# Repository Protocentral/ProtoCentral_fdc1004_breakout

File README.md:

Protocentral FDC1004 capacitance sensor breakout board
================================

### Don't have one? [Buy it here](https://protocentral.com/product/protocentral-fdc1004-capacitance-sensor-breakout-board/)
### Looking for a more integrated solution? [Check out our FDC1004 & ESP32-S3 based Sensything CAP](https://protocentral.com/product/protocentral-sensything-cap-wireless-pulse-sensor-kit-based-on-afe4400-esp32/)

The FDC1004 is a single-chip IC for capacitance measurement for application including proximity sensing and liquid level sensing. This is based on the concept of measuring capacitance of an electrode with respect to ground.

This breakout board contains everything to connect it to an Arduino's I2C pins and it can be connected to any other platform with support for I2C two-wire interfaces.

We have made several cool projects with it including proximity sensing and liquid-level sensing from the outside of a tank. Check out our [Hackster page](https://www.hackster.io/team-protocentral/non-contact-capacitive-liquid-level-sensing-using-fdc1004-9333c7) for the detailed project description.

## Hardware Setup
Connection with the Arduino board is as follows:

|FDC1004 pin label| Arduino Connection  |Pin Function      |
 |:-----------------: |:---------------------:|:------------------:|
 | GND                | GND                   |  GND               |
 | SCL                | A5                    |  Serial Clock      |
 | Vcc                | 5V                    |  Power             |
 | SDA                | A4                    |  Serial Data       |

## Software Features

### Multiple I2C Interface Support
The library now supports using different I2C interfaces (Wire, Wire1, etc.) on boards that have multiple I2C ports like ESP32, Arduino Mega, etc.

#### Basic Usage (Default Wire Interface)
```cpp
#include <Wire.h>
#include <Protocentral_FDC1004.h>

FDC1004 sensor(FDC1004_RATE_100HZ);

void setup() {
    Wire.begin();
    sensor.begin();
}
```

#### Custom I2C Interface Usage
```cpp
#include <Wire.h>
#include <Protocentral_FDC1004.h>

// Method 1: TwoWire pointer as first parameter
FDC1004 sensor(&Wire1, FDC1004_RATE_100HZ);

// Method 2: TwoWire pointer as third parameter
// FDC1004 sensor(FDC1004_RATE_100HZ, FDC1004_I2C_ADDRESS, &Wire1);

void setup() {
    Wire1.begin(); // or Wire1.begin(SDA_PIN, SCL_PIN) for ESP32
    sensor.begin();
}
```

## For further details, refer [the documentation on FDC1004 breakout board](https://docs.protocentral.com/getting-started-with-FDC1004/)

## Contributors & Acknowledgments

We appreciate contributions from our community that help improve this library. Special thanks to:

- **@Benicz** - For identifying and reporting the critical CAPDAC hardware configuration bug (v2.0.1).

If you've contributed to this project, please let us know!

License Information
===================

This product is open source! Both, our hardware and software are open source and licensed under the following licenses:

Hardware
---------

**All hardware is released under [Creative Commons Share-alike 4.0 International](http://creativecommons.org/licenses/by-sa/4.0/).**

You are free to:

* Share — copy and redistribute the material in any medium or format
* Adapt — remix, transform, and build upon the material for any purpose, even commercially.
The licensor cannot revoke these freedoms as long as you follow the license terms.

Under the following terms:

* Attribution — You must give appropriate credit, provide a link to the license, and indicate if changes were made. You may do so in any reasonable manner, but not in any way that suggests the licensor endorses you or your use.
* ShareAlike — If you remix, transform, or build upon the material, you must distribute your contributions under the same license as the original.

Software
--------

**All software is released under the MIT License(http://opensource.org/licenses/MIT).**

THE SOFTWARE IS PROVIDED "AS IS", WITHOUT WARRANTY OF ANY KIND, EXPRESS OR IMPLIED, INCLUDING BUT NOT LIMITED TO THE WARRANTIES OF MERCHANTABILITY, FITNESS FOR A PARTICULAR PURPOSE AND NONINFRINGEMENT. IN NO EVENT SHALL THE AUTHORS OR COPYRIGHT HOLDERS BE LIABLE FOR ANY CLAIM, DAMAGES OR OTHER LIABILITY, WHETHER IN AN ACTION OF CONTRACT, TORT OR OTHERWISE, ARISING FROM, OUT OF OR IN CONNECTION WITH THE SOFTWARE OR THE USE OR OTHER DEALINGS IN THE SOFTWARE.

Please check [*LICENSE.md*](LICENSE.md) for detailed license descriptions.

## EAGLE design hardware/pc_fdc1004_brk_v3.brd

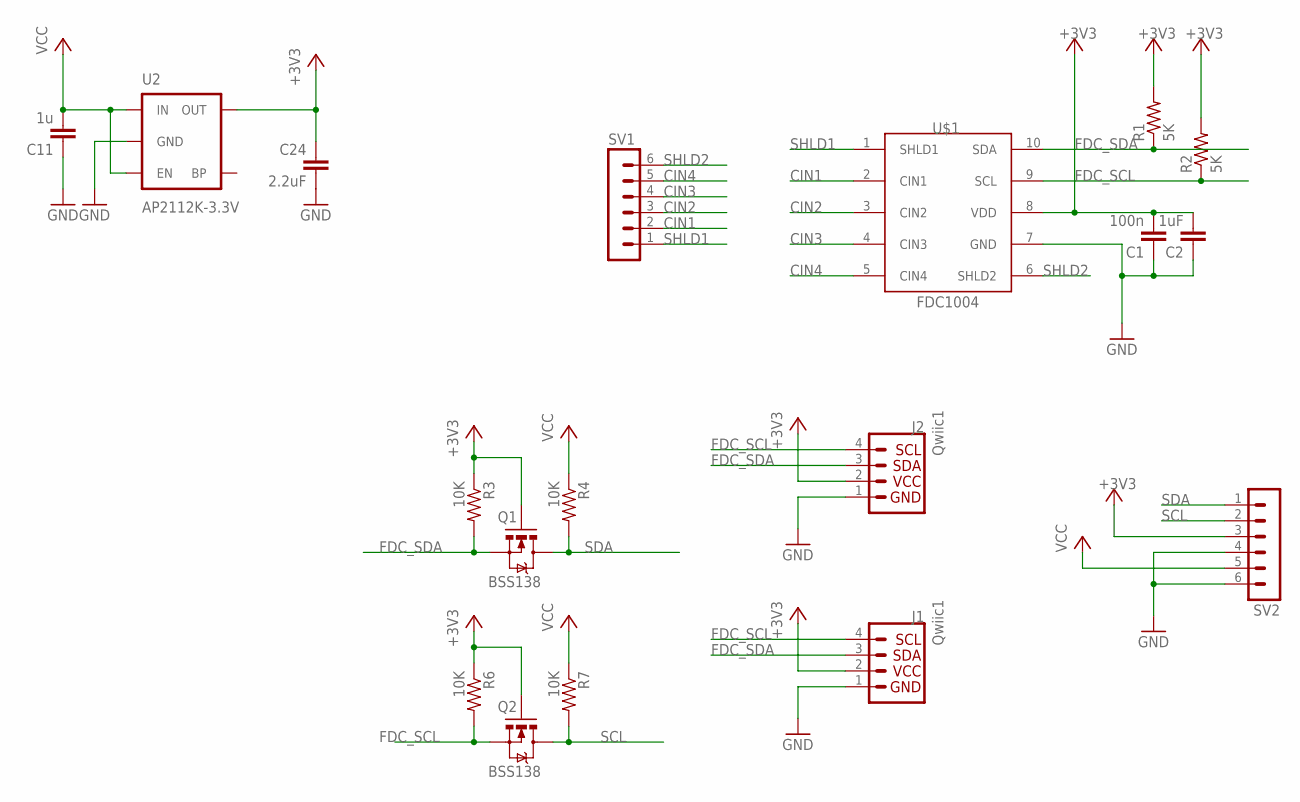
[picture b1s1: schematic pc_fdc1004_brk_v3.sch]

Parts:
C1: 100n; C0805
C2: 1uF; C0805
C11: 1u; C0402
C24: 2.2uF; C0402
J1, J2: Qwiic1; 1X04_1MM_RA
Q1, Q2: BSS138; SOT23-3
R1, R2: 5K; R0805
R3, R4, R6, R7: 10K; 0603-RES
SV1, SV2: MA06-1
U2: AP2112K-3.3V; SOT23-5
U$1: FDC1004; VSSOP-10

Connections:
+3V3: C1.2, C2.2, C24.1, J1.2, J2.2, Q1.1 (G), Q2.1 (G), R1.2, R2.2, R3.1, R6.1, SV2.3, U2.5 (OUT), U$1.8 (VDD)
CIN1: SV1.2, U$1.2 (CIN1)
CIN2: SV1.3, U$1.3 (CIN2)
CIN3: SV1.4, U$1.4 (CIN3)
CIN4: SV1.5, U$1.5 (CIN4)
FDC_SCL: J1.4, J2.4, Q2.2 (S), R2.1, R6.2, U$1.9 (SCL)
FDC_SDA: J1.3, J2.3, Q1.2 (S), R1.1, R3.2, U$1.10 (SDA)
GND: C1.1, C2.1, C11.1, C24.2, J1.1, J2.1, SV2.4, SV2.6, U2.2 (GND), U$1.7 (GND)
SCL: Q2.3 (D), R7.2, SV2.2
SDA: Q1.3 (D), R4.2, SV2.1
SHLD1: SV1.1, U$1.1 (SHLD1)
SHLD2: SV1.6, U$1.6 (SHLD2)
VCC: C11.2, R4.1, R7.1, SV2.5, U2.1 (IN), U2.3 (EN)

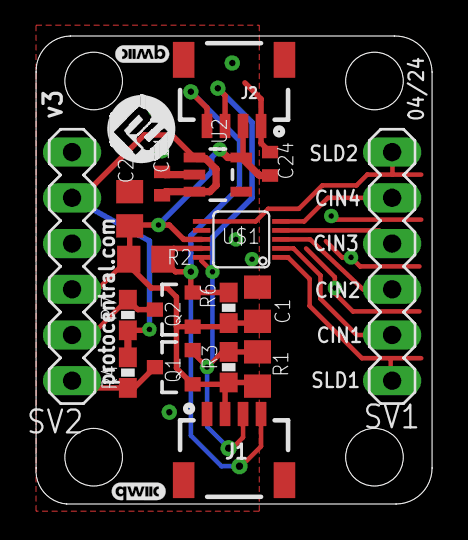
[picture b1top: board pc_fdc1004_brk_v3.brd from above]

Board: 2 copper layers, 22.0 x 26.0 mm, 22 parts (1 on the bottom side), 13 nets.

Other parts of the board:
U$2, U$3: QWIIC_3MM
U$4: PCROUNDLOGO
U$5: PCLOG_SMALL_V3

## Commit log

2016-12-17 Added hardware schematics
2016-12-19 updated arduino library
2016-12-19 Set theme jekyll-theme-cayman
2018-04-18 Updated broken links, images
2018-04-18 Add library format, folder reorg
2018-04-19 Corrected release tag
2023-09-30 Remove begin/endTransmission() around Wire.read()
2023-09-30 Add missing return statement
2024-10-17 schematics,images and readme updated
2024-10-22 FDC1004 documentation link updated
2024-11-29 folders reorganized, workflow added
2024-11-29 library properties corrected
2024-11-29 cpp file updated
2025-07-17 Code refactoring
    - ✅ Restructured code into logical sections with clear documentation
    - ✅ Implemented robust error handling throughout
    - ✅ Added automatic CAPDAC adjustment algorithm
    - ✅ Improved I2C communication with proper error checking
    - ✅ Created conversion utilities for different units
    - ✅ Added input validation for all parameters
2025-07-17 Removed auto docs
2025-07-18 Fix enum declaration issue
2025-07-18 Add new example for multichannel acquisition
2025-07-19 Updated both examples
2025-07-19 Add support for other Twowire interfaces
2025-07-19 Updated version
2025-11-11 Fix CAPDAC issue
2025-11-11 Bump version
2025-11-12 Add Sensything CAP link
2026-01-26 Properly using the 24-bit value
2026-01-27 convertToPicofarads revised

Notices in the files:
README.md:
CC-BY-SA-4.0
parts and their libraries:
SparkFun-PowerIC: Licensing: Creative Commons ShareAlike 4.0 International - https://creativecommons.org/licenses/by-sa/4.0
